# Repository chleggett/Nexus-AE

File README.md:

Please use these available resources:
- [Canonical Documentation](https://clectric.diy/Nexus-AE/)
- [Community Wiki](https://github.com/clectric-diy/Nexus-AE/wiki)
- [clectric.diy Discussions](https://github.com/orgs/clectric-diy/discussions)

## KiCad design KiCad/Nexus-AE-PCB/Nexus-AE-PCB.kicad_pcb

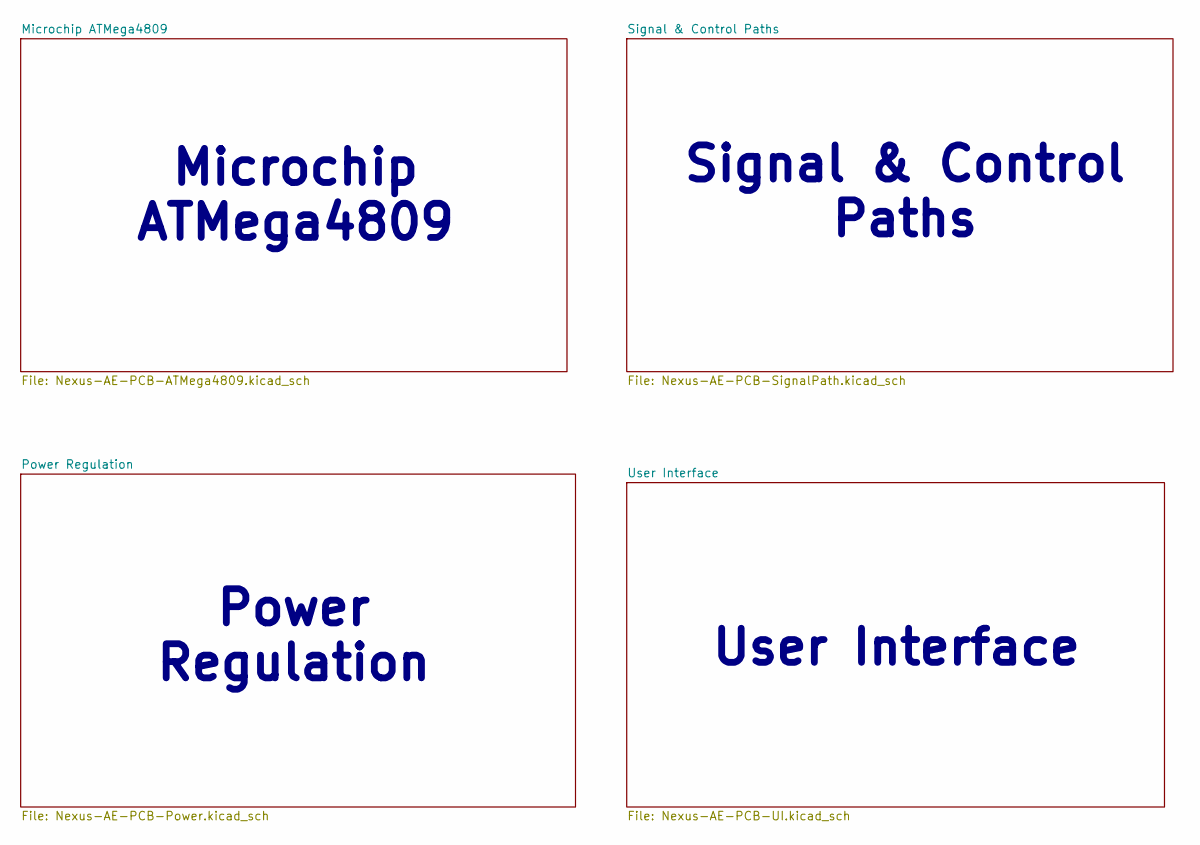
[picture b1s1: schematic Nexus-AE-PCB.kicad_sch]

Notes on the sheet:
User Interface
Signal & Control Paths
Power Regulation
Microchip ATMega4809

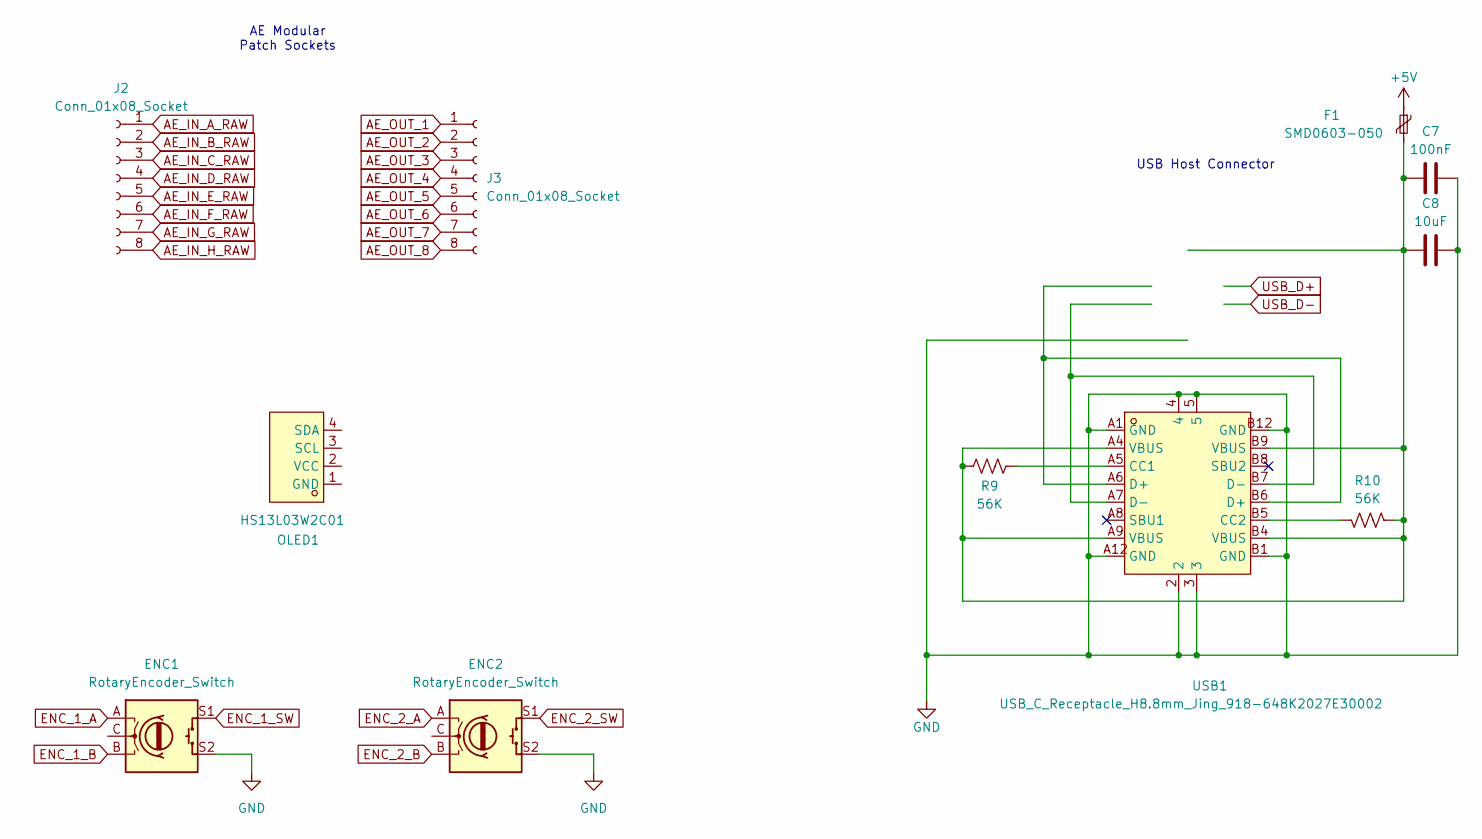
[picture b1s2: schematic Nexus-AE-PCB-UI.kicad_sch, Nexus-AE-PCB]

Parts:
C7: 100nF; C_0402_1005Metric
C8: 10uF; C_0402_1005Metric
ENC1, ENC2: RotaryEncoder_Switch; RotaryEncoder_Alps_EC11E-Switch_Vertical_H20mm
F1: SMD0603-050; Fuse_0603_1608Metric
J2, J3: Conn_01x08_Socket; PinSocket_1x08_P2.54mm_Vertical
OLED1: HS13L03W2C01; OLED-TH_L35.4-W33.5_HS13L03W2C01; MPN HS13L03W2C01; LCSC Part C7465997
R9, R10: 56K; R_0402_1005Metric
USB1: USB_C_Receptacle_H8.8mm_Jing_918-648K2027E30002; LCSC Part C5139026

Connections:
+5V: F1.1; also elsewhere on the board
AE_IN_A_RAW: J2.1; also elsewhere on the board
AE_IN_B_RAW: J2.2; also elsewhere on the board
AE_IN_C_RAW: J2.3; also elsewhere on the board
AE_IN_D_RAW: J2.4; also elsewhere on the board
AE_IN_E_RAW: J2.5; also elsewhere on the board
AE_IN_F_RAW: J2.6; also elsewhere on the board
AE_IN_G_RAW: J2.7; also elsewhere on the board
AE_IN_H_RAW: J2.8; also elsewhere on the board
AE_OUT_1: J3.1; also elsewhere on the board
AE_OUT_2: J3.2; also elsewhere on the board
AE_OUT_3: J3.3; also elsewhere on the board
AE_OUT_4: J3.4; also elsewhere on the board
AE_OUT_5: J3.5; also elsewhere on the board
AE_OUT_6: J3.6; also elsewhere on the board
AE_OUT_7: J3.7; also elsewhere on the board
AE_OUT_8: J3.8; also elsewhere on the board
ENC_1_A: ENC1.A; also elsewhere on the board
ENC_1_B: ENC1.B; also elsewhere on the board
ENC_1_SW: ENC1.S1; also elsewhere on the board
ENC_2_A: ENC2.A; also elsewhere on the board
ENC_2_B: ENC2.B; also elsewhere on the board
ENC_2_SW: ENC2.S1; also elsewhere on the board
GND: C7.2, C8.2, ENC1.S2, ENC2.S2, USB1.2, USB1.3, USB1.4, USB1.5, USB1.A1 (GND), USB1.A12 (GND), USB1.B1 (GND), USB1.B12 (GND); also elsewhere on the board
unnamed: C7.1, C8.1, F1.2, R9.1, R10.1, USB1.A4 (VBUS), USB1.A9 (VBUS), USB1.B4 (VBUS), USB1.B9 (VBUS)
unnamed: R9.2, USB1.A5 (CC1)
unnamed: R10.2, USB1.B5 (CC2)
unnamed: USB1.A6 (D+), USB1.B6 (D+)
unnamed: USB1.A7 (D-), USB1.B7 (D-)

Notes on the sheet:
AE Modular Patch Sockets
USB Host Connector

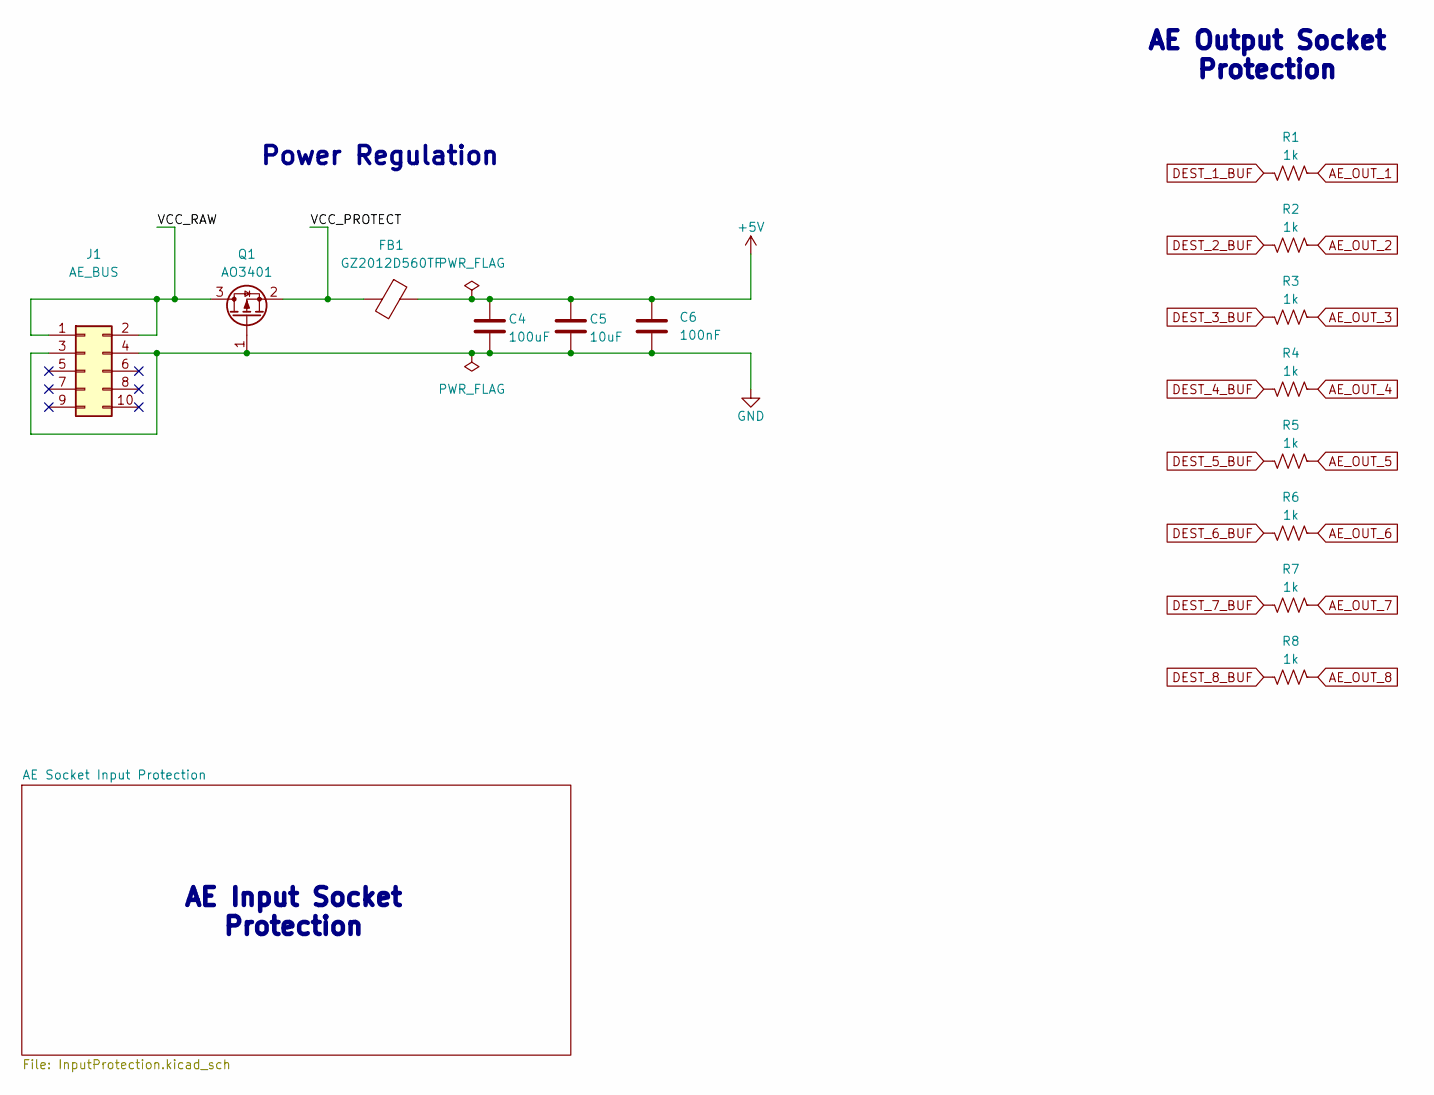
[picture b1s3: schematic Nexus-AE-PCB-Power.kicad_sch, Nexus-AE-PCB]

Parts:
C4: 100uF; C_0402_1005Metric
C5: 10uF; C_0402_1005Metric
C6: 100nF; C_0402_1005Metric
FB1: GZ2012D560TF; L_0805_2012Metric
J1: AE_BUS; PinHeader_2x05_P2.54mm_Vertical
Q1: AO3401; SOT-23
R1, R2, R3, R4, R5, R6, R7, R8: 1k; R_0402_1005Metric

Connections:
+5V: C4.1, C5.1, C6.1, FB1.1; also elsewhere on the board
/Power Regulation/VCC_PROTECT: FB1.2, Q1.2 (S)
/Power Regulation/VCC_RAW: J1.1, J1.2, Q1.3 (D)
AE_OUT_1: R1.1; also elsewhere on the board
AE_OUT_2: R2.1; also elsewhere on the board
AE_OUT_3: R3.1; also elsewhere on the board
AE_OUT_4: R4.1; also elsewhere on the board
AE_OUT_5: R5.1; also elsewhere on the board
AE_OUT_6: R6.1; also elsewhere on the board
AE_OUT_7: R7.1; also elsewhere on the board
AE_OUT_8: R8.1; also elsewhere on the board
DEST_1_BUF: R1.2; also elsewhere on the board
DEST_2_BUF: R2.2; also elsewhere on the board
DEST_3_BUF: R3.2; also elsewhere on the board
DEST_4_BUF: R4.2; also elsewhere on the board
DEST_5_BUF: R5.2; also elsewhere on the board
DEST_6_BUF: R6.2; also elsewhere on the board
DEST_7_BUF: R7.2; also elsewhere on the board
DEST_8_BUF: R8.2; also elsewhere on the board
GND: C4.2, C5.2, C6.2, J1.3, J1.4, Q1.1 (G); also elsewhere on the board

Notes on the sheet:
AE Output Socket Protection
Power Regulation
AE Input Socket Protection

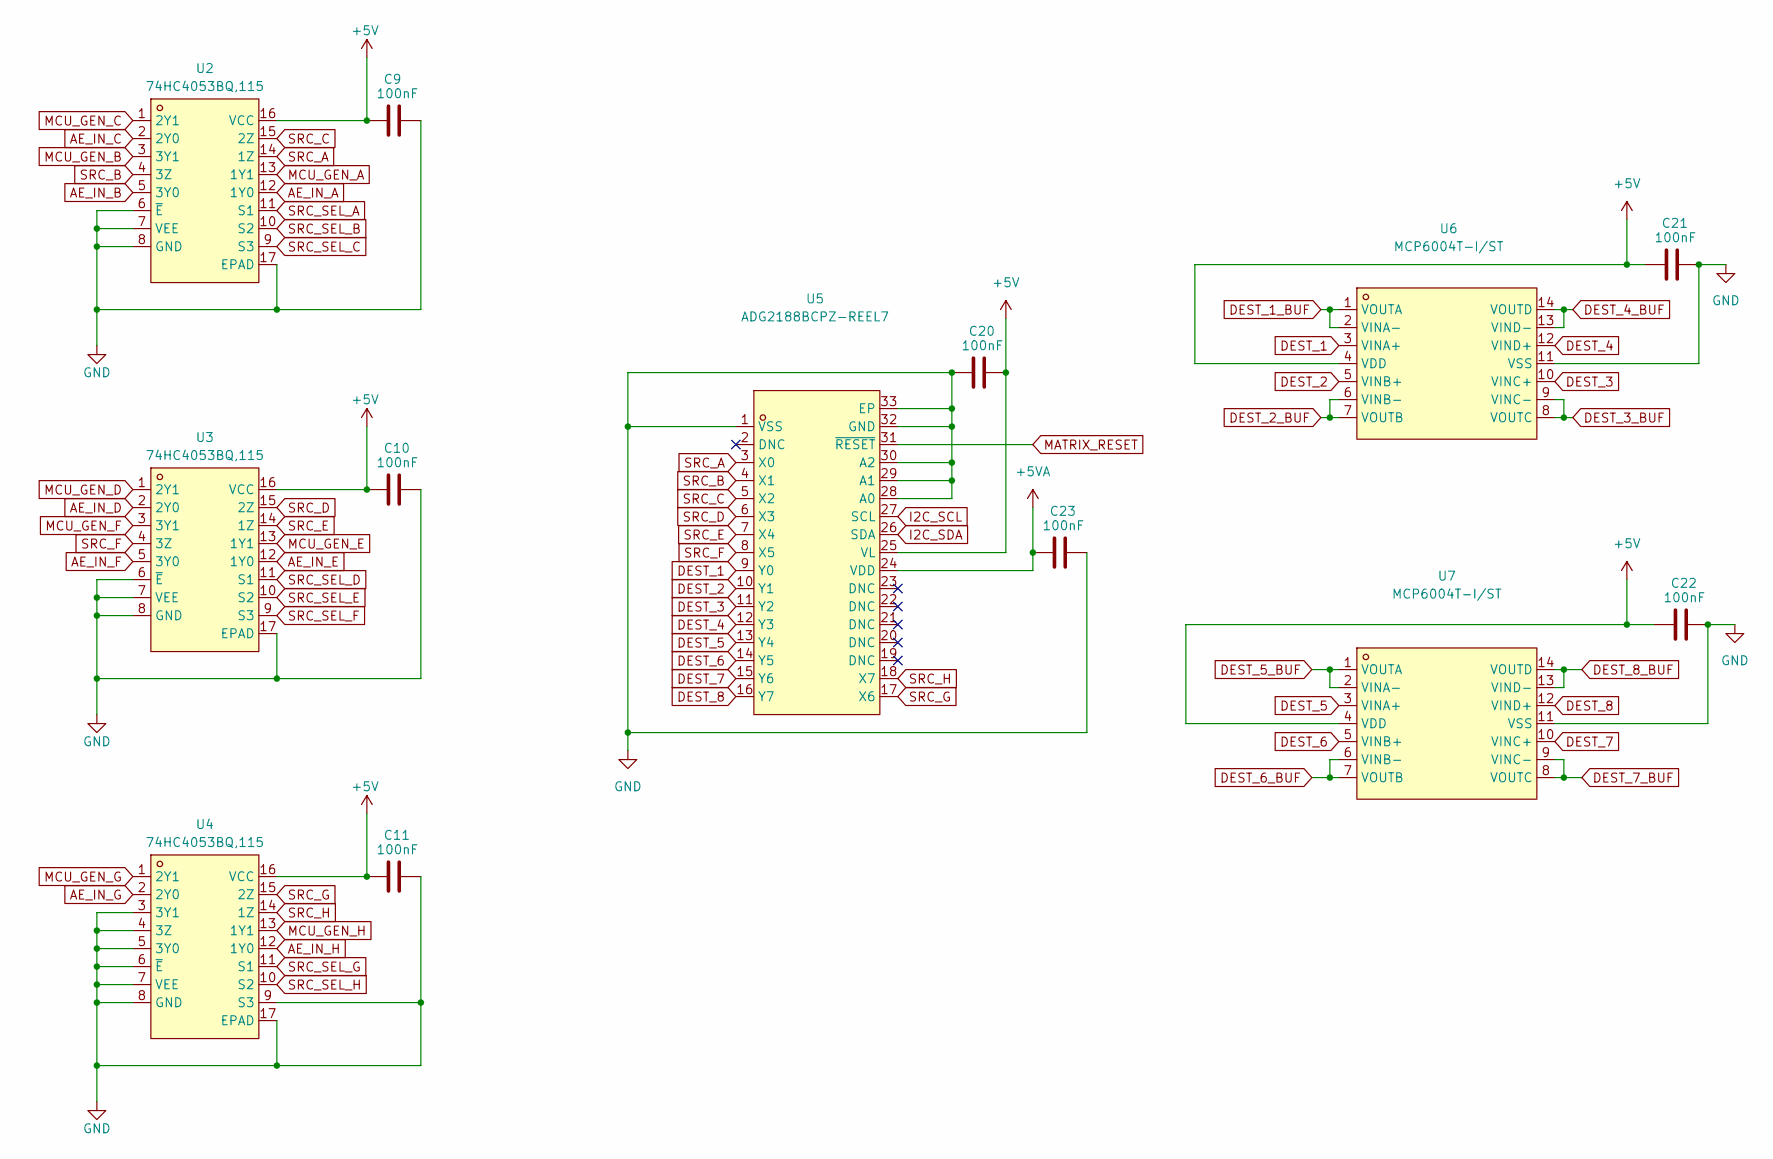
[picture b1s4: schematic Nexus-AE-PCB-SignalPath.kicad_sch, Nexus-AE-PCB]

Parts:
C9, C10, C11, C20, C21, C22, C23: 100nF; C_0402_1005Metric
U2, U3, U4: 74HC4053BQ,115; DHVQFN-16_L3.5-W2.5-P0.50-BL-EP; MPN 74HC4053BQ,115; LCSC Part C128433
U5: ADG2188BCPZ-REEL7; LFCSP-32_L5.0-W5.0-P0.50-TL-EP3.1; MPN ADG2188BCPZ-REEL7; LCSC Part C579043
U6, U7: MCP6004T-I/ST; TSSOP-14_L5.0-W4.4-P0.65-LS6.4-BL; MPN MCP6004T-I/ST; LCSC Part C50282

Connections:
+5V: C9.1, C10.1, C11.1, C20.2, C21.1, C22.1, U2.16 (VCC), U3.16 (VCC), U4.16 (VCC), U5.25 (VL), U6.4 (VDD), U7.4 (VDD); also elsewhere on the board
+5VA: C23.1, U5.24 (VDD); also elsewhere on the board
AE_IN_A: U2.12 (1Y0); also elsewhere on the board
AE_IN_B: U2.5 (3Y0); also elsewhere on the board
AE_IN_C: U2.2 (2Y0); also elsewhere on the board
AE_IN_D: U3.2 (2Y0); also elsewhere on the board
AE_IN_E: U3.12 (1Y0); also elsewhere on the board
AE_IN_F: U3.5 (3Y0); also elsewhere on the board
AE_IN_G: U4.2 (2Y0); also elsewhere on the board
AE_IN_H: U4.12 (1Y0); also elsewhere on the board
DEST_1: U5.9 (Y0), U6.3 (VINA+)
DEST_1_BUF: U6.1 (VOUTA), U6.2 (VINA-); also elsewhere on the board
DEST_2: U5.10 (Y1), U6.5 (VINB+)
DEST_2_BUF: U6.6 (VINB-), U6.7 (VOUTB); also elsewhere on the board
DEST_3: U5.11 (Y2), U6.10 (VINC+)
DEST_3_BUF: U6.8 (VOUTC), U6.9 (VINC-); also elsewhere on the board
DEST_4: U5.12 (Y3), U6.12 (VIND+)
DEST_4_BUF: U6.13 (VIND-), U6.14 (VOUTD); also elsewhere on the board
DEST_5: U5.13 (Y4), U7.3 (VINA+)
DEST_5_BUF: U7.1 (VOUTA), U7.2 (VINA-); also elsewhere on the board
DEST_6: U5.14 (Y5), U7.5 (VINB+)
DEST_6_BUF: U7.6 (VINB-), U7.7 (VOUTB); also elsewhere on the board
DEST_7: U5.15 (Y6), U7.10 (VINC+)
DEST_7_BUF: U7.8 (VOUTC), U7.9 (VINC-); also elsewhere on the board
DEST_8: U5.16 (Y7), U7.12 (VIND+)
DEST_8_BUF: U7.13 (VIND-), U7.14 (VOUTD); also elsewhere on the board
GND: C9.2, C10.2, C11.2, C20.1, C21.2, C22.2, C23.2, U2.6 (~E), U2.7 (VEE), U2.8 (GND), U2.17 (EPAD), U3.6 (~E), U3.7 (VEE), U3.8 (GND), U3.17 (EPAD), U4.3 (3Y1), U4.4 (3Z), U4.5 (3Y0), U4.6 (~E), U4.7 (VEE), U4.8 (GND), U4.9 (S3), U4.17 (EPAD), U5.1 (VSS), U5.28 (A0), U5.29 (A1), U5.30 (A2), U5.32 (GND), U5.33 (EP), U6.11 (VSS), U7.11 (VSS); also elsewhere on the board
I2C_SCL: U5.27 (SCL); also elsewhere on the board
I2C_SDA: U5.26 (SDA); also elsewhere on the board
MATRIX_RESET: U5.31 (~RESET); also elsewhere on the board
MCU_GEN_A: U2.13 (1Y1); also elsewhere on the board
MCU_GEN_B: U2.3 (3Y1); also elsewhere on the board
MCU_GEN_C: U2.1 (2Y1); also elsewhere on the board
MCU_GEN_D: U3.1 (2Y1); also elsewhere on the board
MCU_GEN_E: U3.13 (1Y1); also elsewhere on the board
MCU_GEN_F: U3.3 (3Y1); also elsewhere on the board
MCU_GEN_G: U4.1 (2Y1); also elsewhere on the board
MCU_GEN_H: U4.13 (1Y1); also elsewhere on the board
SRC_A: U2.14 (1Z), U5.3 (X0)
SRC_B: U2.4 (3Z), U5.4 (X1)
SRC_C: U2.15 (2Z), U5.5 (X2)
SRC_D: U3.15 (2Z), U5.6 (X3)
SRC_E: U3.14 (1Z), U5.7 (X4)
SRC_F: U3.4 (3Z), U5.8 (X5)
SRC_G: U4.15 (2Z), U5.17 (X6)
SRC_H: U4.14 (1Z), U5.18 (X7)
SRC_SEL_A: U2.11 (S1); also elsewhere on the board
SRC_SEL_B: U2.10 (S2); also elsewhere on the board
SRC_SEL_C: U2.9 (S3); also elsewhere on the board
SRC_SEL_D: U3.11 (S1); also elsewhere on the board
SRC_SEL_E: U3.10 (S2); also elsewhere on the board
SRC_SEL_F: U3.9 (S3); also elsewhere on the board
SRC_SEL_G: U4.11 (S1); also elsewhere on the board
SRC_SEL_H: U4.10 (S2); also elsewhere on the board

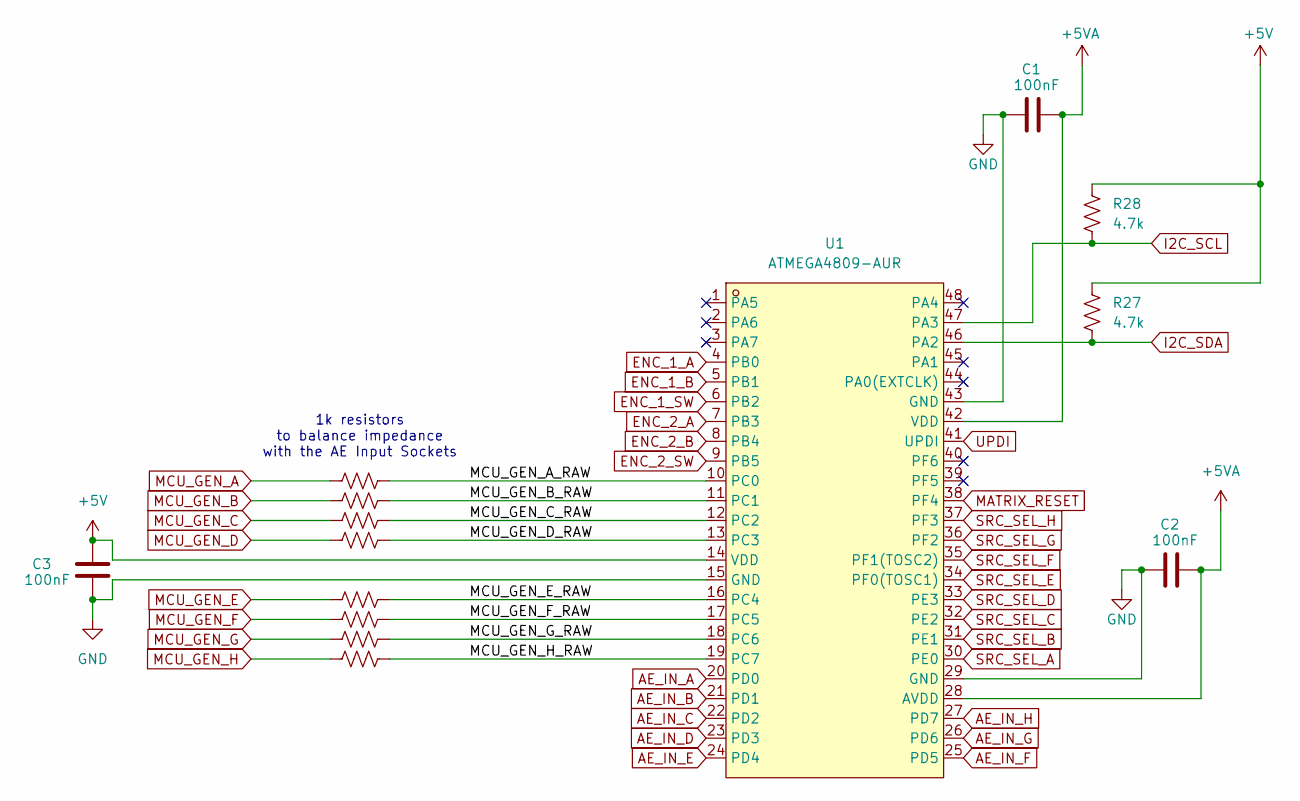
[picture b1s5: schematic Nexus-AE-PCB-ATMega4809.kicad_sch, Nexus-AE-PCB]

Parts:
C1, C2, C3: 100nF; C_0402_1005Metric
R27, R28: 4.7k; R_0402_1005Metric
R29, R30, R31, R32, R33, R34, R35, R36: 1k; R_0402_1005Metric
U1: ATMEGA4809-AUR; TQFP-48_L7.0-W7.0-P0.50-LS9.0-BL; MPN ATMEGA4809-AUR; LCSC Part C2055381

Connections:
+5V: C3.2, R27.1, R28.1, U1.14 (VDD); also elsewhere on the board
+5VA: C1.2, C2.2, U1.28 (AVDD), U1.42 (VDD); also elsewhere on the board
/Microchip ATMega4809/MCU_GEN_A_RAW: R29.2, U1.10 (PC0)
/Microchip ATMega4809/MCU_GEN_B_RAW: R30.2, U1.11 (PC1)
/Microchip ATMega4809/MCU_GEN_C_RAW: R31.2, U1.12 (PC2)
/Microchip ATMega4809/MCU_GEN_D_RAW: R32.2, U1.13 (PC3)
/Microchip ATMega4809/MCU_GEN_E_RAW: R33.2, U1.16 (PC4)
/Microchip ATMega4809/MCU_GEN_F_RAW: R34.2, U1.17 (PC5)
/Microchip ATMega4809/MCU_GEN_G_RAW: R35.2, U1.18 (PC6)
/Microchip ATMega4809/MCU_GEN_H_RAW: R36.2, U1.19 (PC7)
AE_IN_A: U1.20 (PD0); also elsewhere on the board
AE_IN_B: U1.21 (PD1); also elsewhere on the board
AE_IN_C: U1.22 (PD2); also elsewhere on the board
AE_IN_D: U1.23 (PD3); also elsewhere on the board
AE_IN_E: U1.24 (PD4); also elsewhere on the board
AE_IN_F: U1.25 (PD5); also elsewhere on the board
AE_IN_G: U1.26 (PD6); also elsewhere on the board
AE_IN_H: U1.27 (PD7); also elsewhere on the board
ENC_1_A: U1.4 (PB0); also elsewhere on the board
ENC_1_B: U1.5 (PB1); also elsewhere on the board
ENC_1_SW: U1.6 (PB2); also elsewhere on the board
ENC_2_A: U1.7 (PB3); also elsewhere on the board
ENC_2_B: U1.8 (PB4); also elsewhere on the board
ENC_2_SW: U1.9 (PB5); also elsewhere on the board
GND: C1.1, C2.1, C3.1, U1.15 (GND), U1.29 (GND), U1.43 (GND); also elsewhere on the board
I2C_SCL: R28.2, U1.47 (PA3); also elsewhere on the board
I2C_SDA: R27.2, U1.46 (PA2); also elsewhere on the board
MATRIX_RESET: U1.38 (PF4); also elsewhere on the board
MCU_GEN_A: R29.1; also elsewhere on the board
MCU_GEN_B: R30.1; also elsewhere on the board
MCU_GEN_C: R31.1; also elsewhere on the board
MCU_GEN_D: R32.1; also elsewhere on the board
MCU_GEN_E: R33.1; also elsewhere on the board
MCU_GEN_F: R34.1; also elsewhere on the board
MCU_GEN_G: R35.1; also elsewhere on the board
MCU_GEN_H: R36.1; also elsewhere on the board
SRC_SEL_A: U1.30 (PE0); also elsewhere on the board
SRC_SEL_B: U1.31 (PE1); also elsewhere on the board
SRC_SEL_C: U1.32 (PE2); also elsewhere on the board
SRC_SEL_D: U1.33 (PE3); also elsewhere on the board
SRC_SEL_E: U1.34 (PF0(TOSC1)); also elsewhere on the board
SRC_SEL_F: U1.35 (PF1(TOSC2)); also elsewhere on the board
SRC_SEL_G: U1.36 (PF2); also elsewhere on the board
SRC_SEL_H: U1.37 (PF3); also elsewhere on the board
UPDI: U1.41 (UPDI)

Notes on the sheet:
1k resistors to balance impedance with the AE Input Sockets

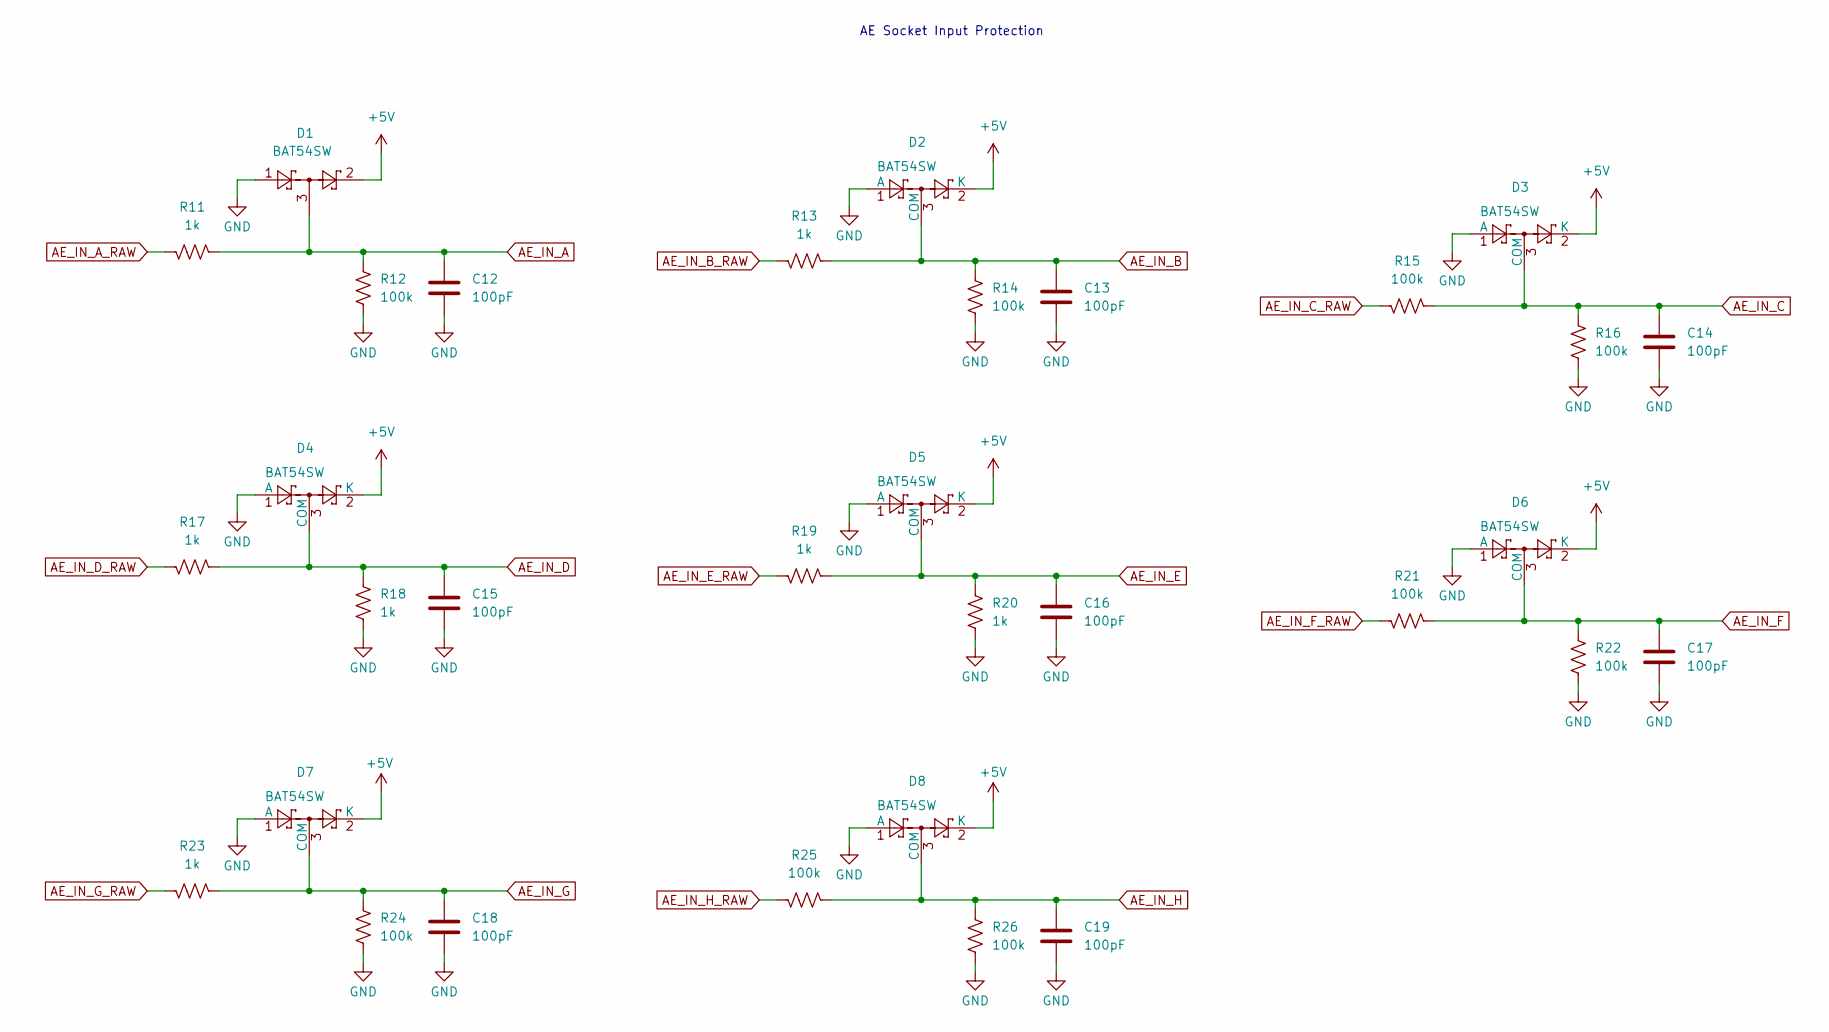
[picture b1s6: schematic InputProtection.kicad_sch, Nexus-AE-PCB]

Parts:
C12, C13, C14, C15, C16, C17, C18, C19: 100pF; C_0402_1005Metric
D1, D2, D3, D4, D5, D6, D7, D8: BAT54SW; SOT-323_SC-70
R11, R13, R17, R18, R19, R20, R23: 1k; R_0402_1005Metric
R12, R14, R15, R16, R21, R22, R24, R25, R26: 100k; R_0402_1005Metric

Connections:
+5V: D1.2 (K), D2.2 (K), D3.2 (K), D4.2 (K), D5.2 (K), D6.2 (K), D7.2 (K), D8.2 (K); also elsewhere on the board
AE_IN_A: C12.1, D1.3 (COM), R11.2, R12.1; also elsewhere on the board
AE_IN_A_RAW: R11.1; also elsewhere on the board
AE_IN_B: C13.1, D2.3 (COM), R13.2, R14.1; also elsewhere on the board
AE_IN_B_RAW: R13.1; also elsewhere on the board
AE_IN_C: C14.1, D3.3 (COM), R15.2, R16.1; also elsewhere on the board
AE_IN_C_RAW: R15.1; also elsewhere on the board
AE_IN_D: C15.1, D4.3 (COM), R17.2, R18.1; also elsewhere on the board
AE_IN_D_RAW: R17.1; also elsewhere on the board
AE_IN_E: C16.1, D5.3 (COM), R19.2, R20.1; also elsewhere on the board
AE_IN_E_RAW: R19.1; also elsewhere on the board
AE_IN_F: C17.1, D6.3 (COM), R21.2, R22.1; also elsewhere on the board
AE_IN_F_RAW: R21.1; also elsewhere on the board
AE_IN_G: C18.1, D7.3 (COM), R23.2, R24.1; also elsewhere on the board
AE_IN_G_RAW: R23.1; also elsewhere on the board
AE_IN_H: C19.1, D8.3 (COM), R25.2, R26.1; also elsewhere on the board
AE_IN_H_RAW: R25.1; also elsewhere on the board
GND: C12.2, C13.2, C14.2, C15.2, C16.2, C17.2, C18.2, C19.2, D1.1 (A), D2.1 (A), D3.1 (A), D4.1 (A), D5.1 (A), D6.1 (A), D7.1 (A), D8.1 (A), R12.2, R14.2, R16.2, R18.2, R20.2, R22.2, R24.2, R26.2; also elsewhere on the board

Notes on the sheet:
AE Socket Input Protection

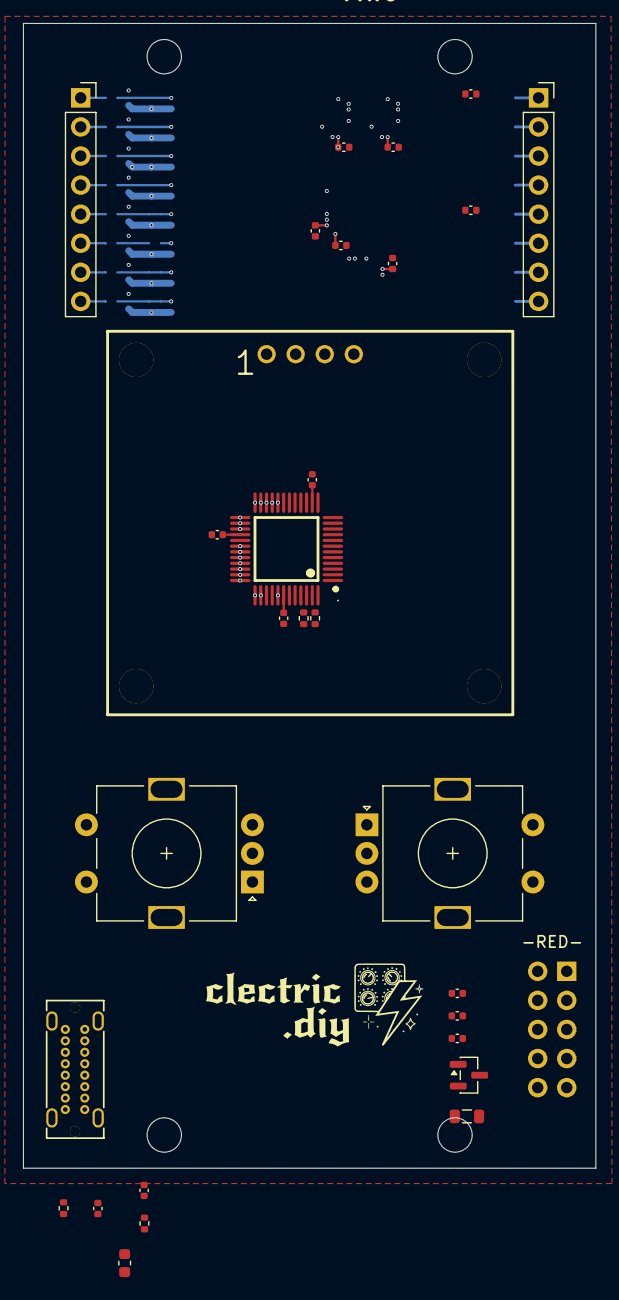
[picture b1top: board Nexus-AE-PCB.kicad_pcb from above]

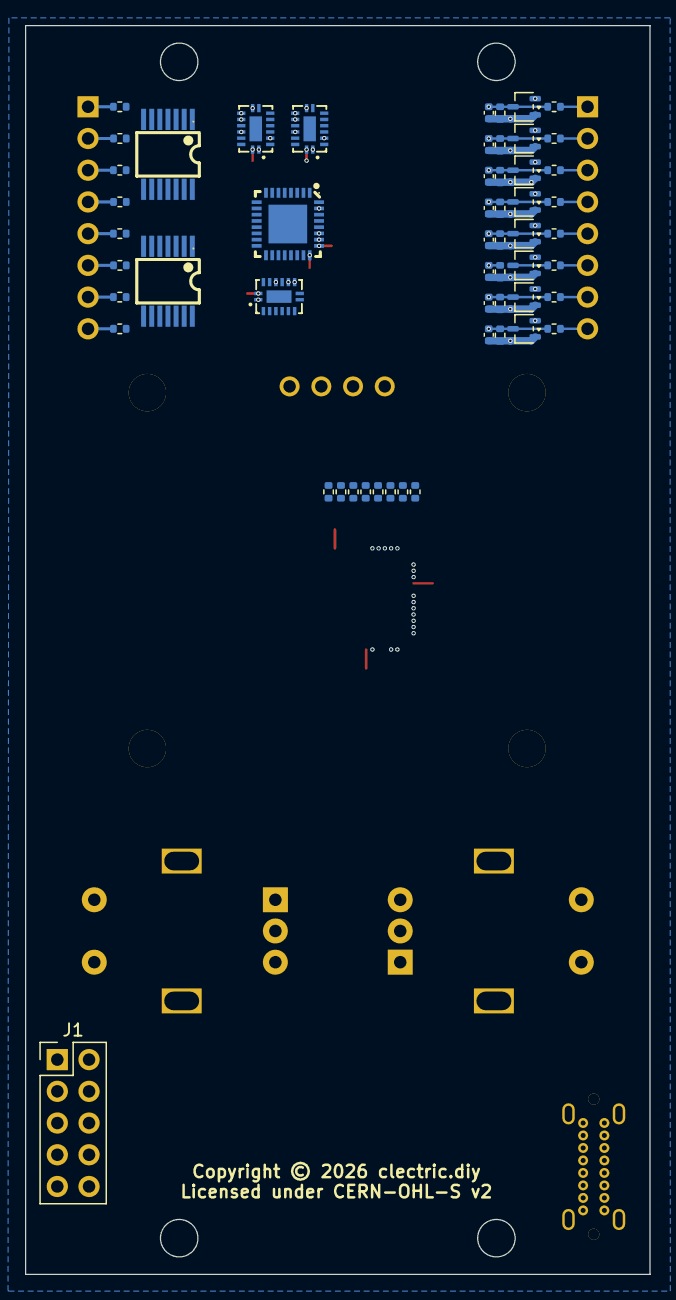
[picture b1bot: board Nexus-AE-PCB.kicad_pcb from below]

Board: 2 copper layers, 50.0 x 100.0 mm, 84 parts (55 on the bottom side), 91 nets.

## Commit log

2026-03-29 Initial README commit
    Added README with detailed product features and functionality.
2026-03-29 Add note about FLUX firmware reprogramming
2026-03-29 Add information about ATmega4808 and ADG2188 ICs
2026-04-03 generalized the README to move away from the Lunetta specific firmware use case.
2026-04-03 Update FLUX firmware link in README
2026-04-11 ignore macOS, backup, and fabrication files
2026-04-11 starting from copy of Spark-AE
2026-04-13 relying on board setup config to set constraints
2026-04-13 PCB and schmeatic are both approx 90% complete
2026-04-26 transitoning to GitHub Pages in docs
2026-04-26 applying CERN-OHL-S license
2026-04-26 adding template for GitHub Pages
2026-04-26 added collaboration and licensing blurbs
2026-04-26 removing duplicated description
2026-04-26 updating description
2026-04-26 adding funding config

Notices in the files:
KiCad/Nexus-AE-PCB/InputProtection.kicad_sch:
Copyright © 2026 clectric.diy Licensed under CERN-OHL-S v2
